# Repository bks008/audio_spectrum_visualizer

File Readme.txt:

Audio Spectrum Visualizer

Samples stereo analog audio and displays the frequency response on an 8x24 dot LED display.

Inputs:
USB-C PD

R/L RCA at audio line level

USB-C comes in at 20V. 
Supply rails:
3.3V digital supply
5V display supply
+/-6V analog supplies. +/-5V after LDO

R/L RCA has two identical channels
Gain stage
Unity gain stage to add offset (0-5V signal)
Anti Aliasing Low Pass Filter stage
Sampled using ADC121S101 over SPI

Digital Section is anything in the Arduino Nano pinout/form factor. Going with an STM32 NUCLEO-L432KC

Nucleo drives LEDs using I2C to three HT16K33A (borrowing architecture from Adafruit). 

Includes rotary encoder for brightness control and pushbutton.

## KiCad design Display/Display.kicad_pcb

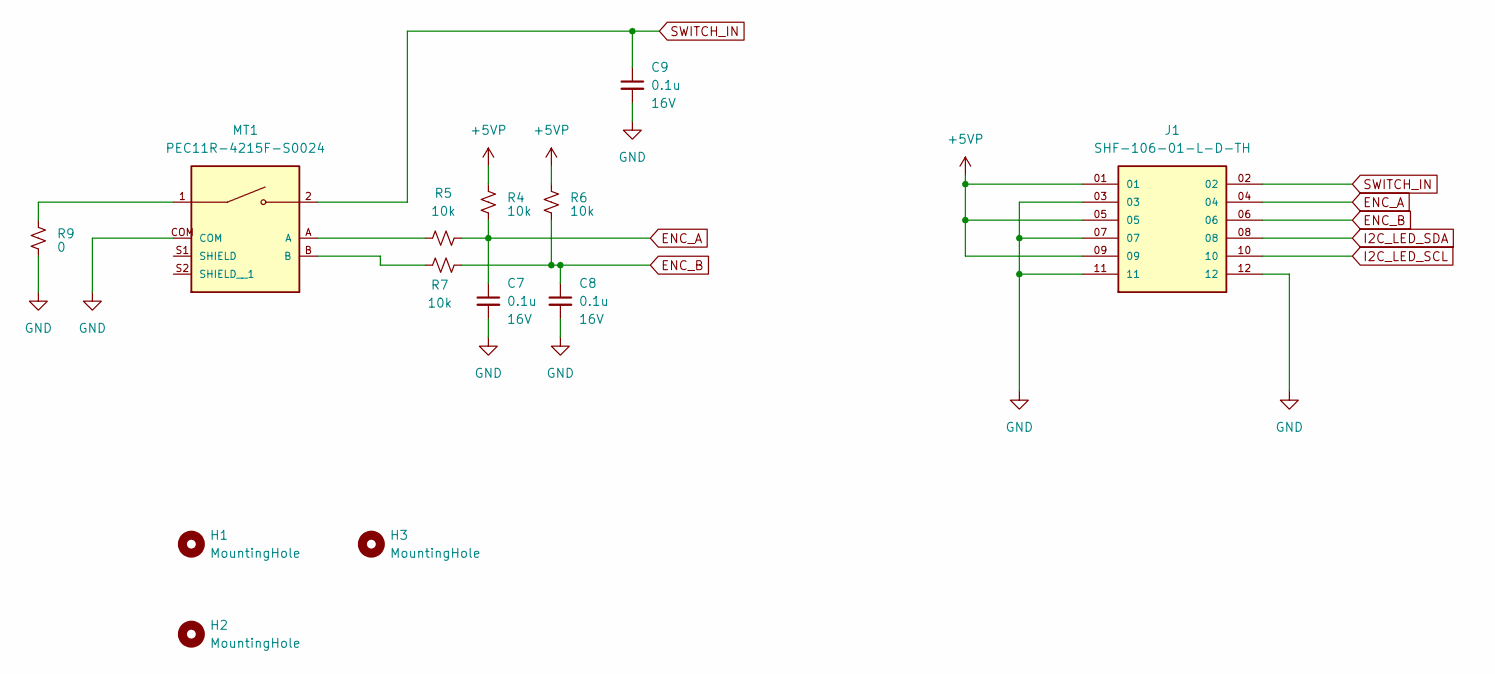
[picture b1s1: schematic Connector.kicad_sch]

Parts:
C7, C8, C9: 0.1u; C_0805_2012Metric_Pad1.18x1.45mm_HandSolder; Voltage 16V; Part Number 0805YC104MAT2A
H1, H2, H3: MountingHole; MountingHole_2.2mm_M2_Pad
J1: SHF-106-01-L-D-TH; SAMTEC_SHF-106-01-L-D-TH; PARTREV R
MT1: PEC11R-4215F-S0024; XDCR_PEC11R-4215F-S0024; PARTREV Rev. 09/19
R4, R5, R6, R7: 10k; R_0805_2012Metric_Pad1.20x1.40mm_HandSolder; Part Number CRCW080510K0FKEA
R9: 0; R_0805_2012Metric_Pad1.20x1.40mm_HandSolder; Part Number CRCW08050000FKEA

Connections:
+5VP: J1.01, J1.05, J1.09, R4.1, R6.1; also elsewhere on the board
ENC_A: C7.1, J1.04, R4.2, R5.2
ENC_B: C8.1, J1.06, R6.2, R7.2
GND: C7.2, C8.2, C9.2, J1.03, J1.07, J1.11, J1.12, MT1.COM, R9.2; also elsewhere on the board
I2C_LED_SCL: J1.10; also elsewhere on the board
I2C_LED_SDA: J1.08; also elsewhere on the board
unnamed: MT1.1, R9.1
unnamed: MT1.A, R5.1
unnamed: MT1.B, R7.1
SWITCH_IN: C9.1, J1.02, MT1.2

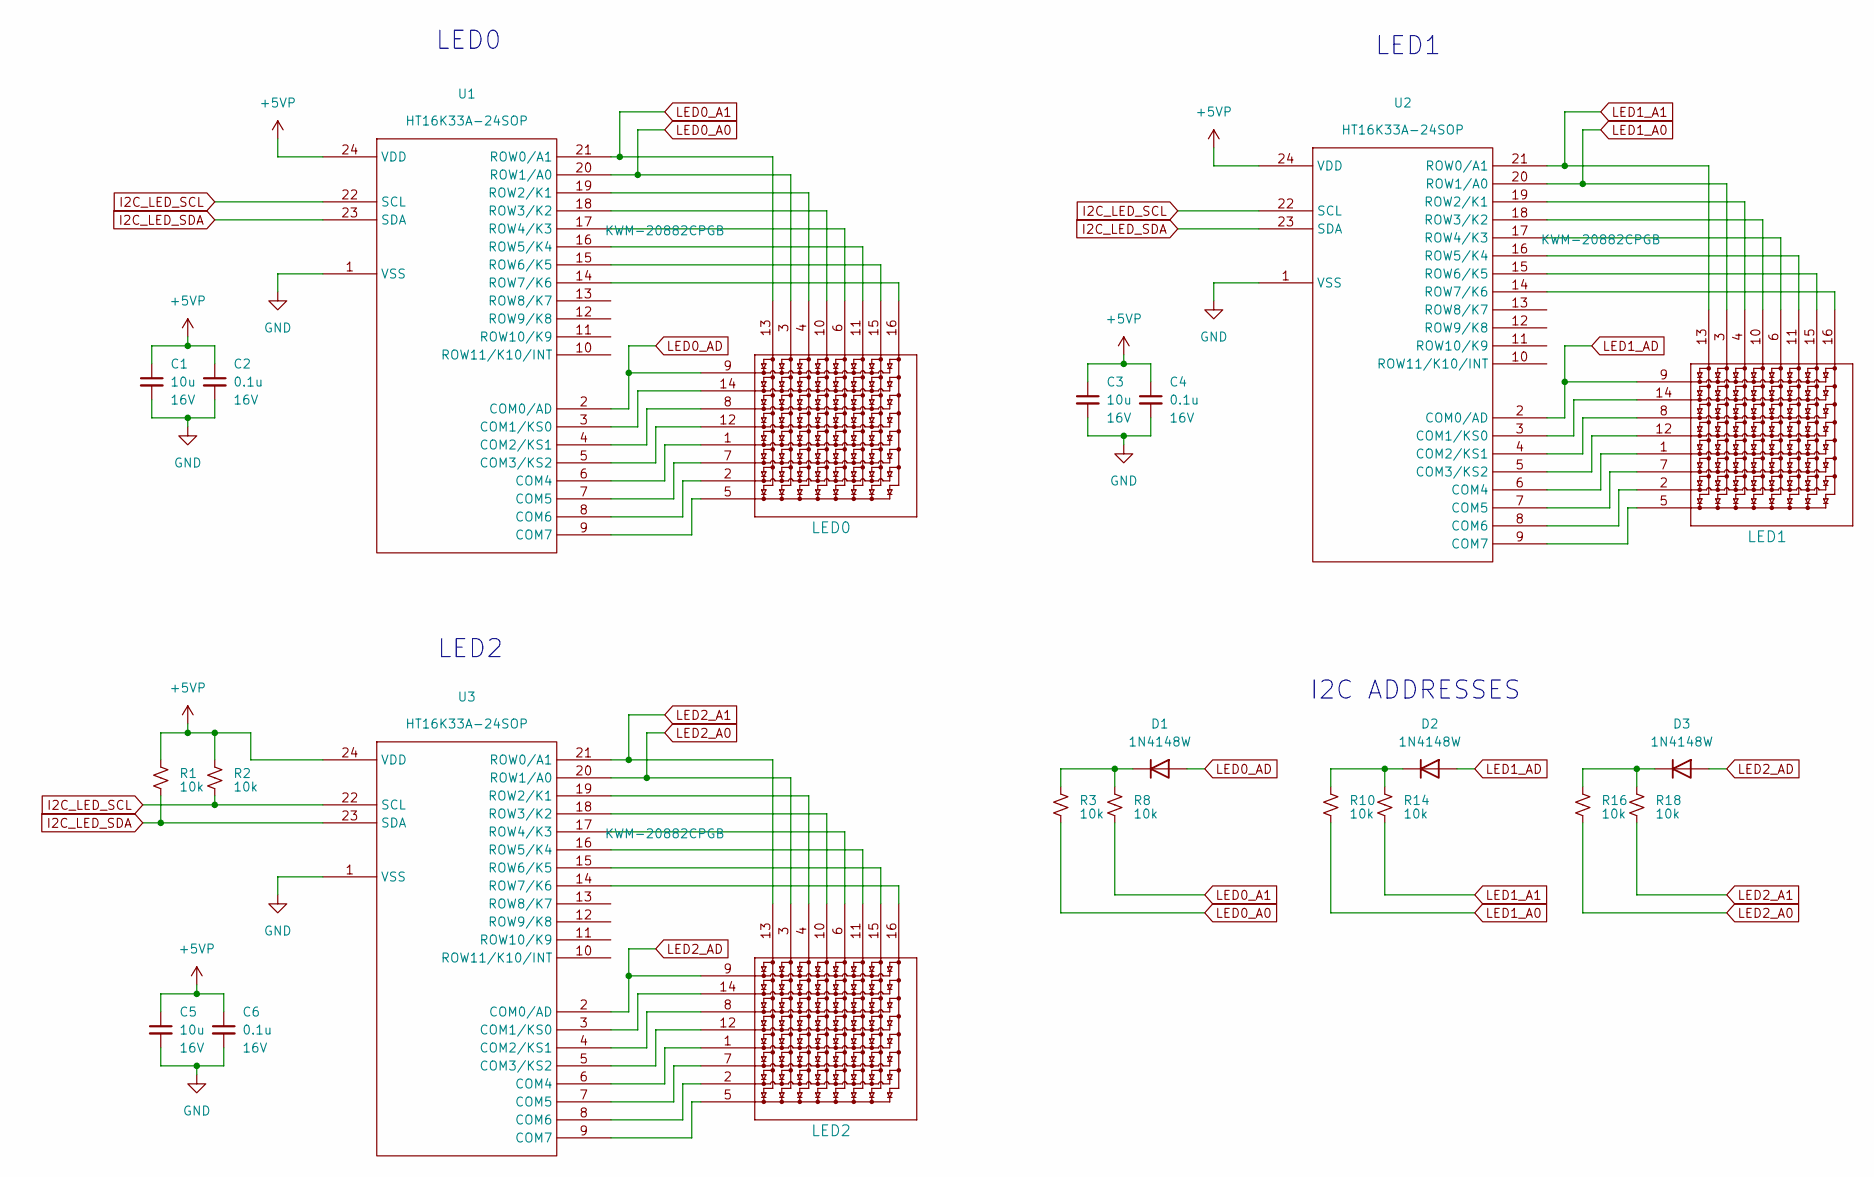
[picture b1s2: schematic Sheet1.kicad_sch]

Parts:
C1, C3, C5: 10u; C_0805_2012Metric_Pad1.18x1.45mm_HandSolder; Voltage 16V; Part Number 0805YC106MAT2A
C2, C4, C6: 0.1u; C_0805_2012Metric_Pad1.18x1.45mm_HandSolder; Voltage 16V; Part Number 0805YC104MAT2A
D1, D2: 1N4148W; D_SOD-523
D3: 1N4148W; D_SOD-523; Part Number 1N4148W
LED0, LED1, LED2: KWM-R30881CBB; KWM-20882AUGB; Part Number KWM-20882CPGB
R1, R2, R3, R8, R10, R14, R16, R18: 10k; R_0805_2012Metric_Pad1.20x1.40mm_HandSolder; Part Number CRCW080510K0FKEA
U1, U2, U3: SOP-24_7.5x15.4mm_P1.27mm; Part Number HT16K33A-24SOP

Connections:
+5VP: C1.1, C2.1, C3.1, C4.1, C5.1, C6.1, R1.1, R2.1, U1.24 (VDD), U2.24 (VDD), U3.24 (VDD); also elsewhere on the board
GND: C1.2, C2.2, C3.2, C4.2, C5.2, C6.2, U1.1 (VSS), U2.1 (VSS), U3.1 (VSS); also elsewhere on the board
I2C_LED_SCL: R2.2, U1.22 (SCL), U2.22 (SCL), U3.22 (SCL); also elsewhere on the board
I2C_LED_SDA: R1.2, U1.23 (SDA), U2.23 (SDA), U3.23 (SDA); also elsewhere on the board
LED0_A0: LED0.3 (ANODE_2), R3.2, U1.20 (ROW1/A0)
LED0_A1: LED0.13 (ANODE_1), R8.2, U1.21 (ROW0/A1)
LED0_AD: D1.2 (A), LED0.9 (CATHODE_1), U1.2 (COM0/AD)
LED1_A0: LED1.3 (ANODE_2), R10.2, U2.20 (ROW1/A0)
LED1_A1: LED1.13 (ANODE_1), R14.2, U2.21 (ROW0/A1)
LED1_AD: D2.2 (A), LED1.9 (CATHODE_1), U2.2 (COM0/AD)
LED2_A0: LED2.3 (ANODE_2), R16.2, U3.20 (ROW1/A0)
LED2_A1: LED2.13 (ANODE_1), R18.2, U3.21 (ROW0/A1)
LED2_AD: D3.2 (A), LED2.9 (CATHODE_1), U3.2 (COM0/AD)
unnamed: D1.1 (K), R3.1, R8.1
unnamed: D2.1 (K), R10.1, R14.1
unnamed: D3.1 (K), R16.1, R18.1
unnamed: LED0.4 (ANODE_3), U1.19 (ROW2/K1)
unnamed: LED0.10 (ANODE_4), U1.18 (ROW3/K2)
unnamed: LED0.6 (ANODE_5), U1.17 (ROW4/K3)
unnamed: LED0.11 (ANODE_6), U1.16 (ROW5/K4)
unnamed: LED0.15 (ANODE_7), U1.15 (ROW6/K5)
unnamed: LED0.16 (ANODE_8), U1.14 (ROW7/K6)
unnamed: LED0.14 (CATHODE_2), U1.3 (COM1/KS0)
unnamed: LED0.8 (CATHODE_3), U1.4 (COM2/KS1)
unnamed: LED0.12 (CATHODE_4), U1.5 (COM3/KS2)
unnamed: LED0.1 (CATHODE_5), U1.6 (COM4)
unnamed: LED0.7 (CATHODE_6), U1.7 (COM5)
unnamed: LED0.2 (CATHODE_7), U1.8 (COM6)
unnamed: LED0.5 (CATHODE_8), U1.9 (COM7)
unnamed: LED1.4 (ANODE_3), U2.19 (ROW2/K1)
unnamed: LED1.10 (ANODE_4), U2.18 (ROW3/K2)
unnamed: LED1.6 (ANODE_5), U2.17 (ROW4/K3)
unnamed: LED1.11 (ANODE_6), U2.16 (ROW5/K4)
unnamed: LED1.15 (ANODE_7), U2.15 (ROW6/K5)
unnamed: LED1.16 (ANODE_8), U2.14 (ROW7/K6)
unnamed: LED1.14 (CATHODE_2), U2.3 (COM1/KS0)
unnamed: LED1.8 (CATHODE_3), U2.4 (COM2/KS1)
unnamed: LED1.12 (CATHODE_4), U2.5 (COM3/KS2)
unnamed: LED1.1 (CATHODE_5), U2.6 (COM4)
unnamed: LED1.7 (CATHODE_6), U2.7 (COM5)
unnamed: LED1.2 (CATHODE_7), U2.8 (COM6)
unnamed: LED1.5 (CATHODE_8), U2.9 (COM7)
unnamed: LED2.4 (ANODE_3), U3.19 (ROW2/K1)
unnamed: LED2.10 (ANODE_4), U3.18 (ROW3/K2)
unnamed: LED2.6 (ANODE_5), U3.17 (ROW4/K3)
unnamed: LED2.11 (ANODE_6), U3.16 (ROW5/K4)
unnamed: LED2.15 (ANODE_7), U3.15 (ROW6/K5)
unnamed: LED2.16 (ANODE_8), U3.14 (ROW7/K6)
unnamed: LED2.14 (CATHODE_2), U3.3 (COM1/KS0)
unnamed: LED2.8 (CATHODE_3), U3.4 (COM2/KS1)
unnamed: LED2.12 (CATHODE_4), U3.5 (COM3/KS2)
unnamed: LED2.1 (CATHODE_5), U3.6 (COM4)
unnamed: LED2.7 (CATHODE_6), U3.7 (COM5)
unnamed: LED2.2 (CATHODE_7), U3.8 (COM6)
unnamed: LED2.5 (CATHODE_8), U3.9 (COM7)

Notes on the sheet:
LED1
I2C ADDRESSES
LED0
LED2

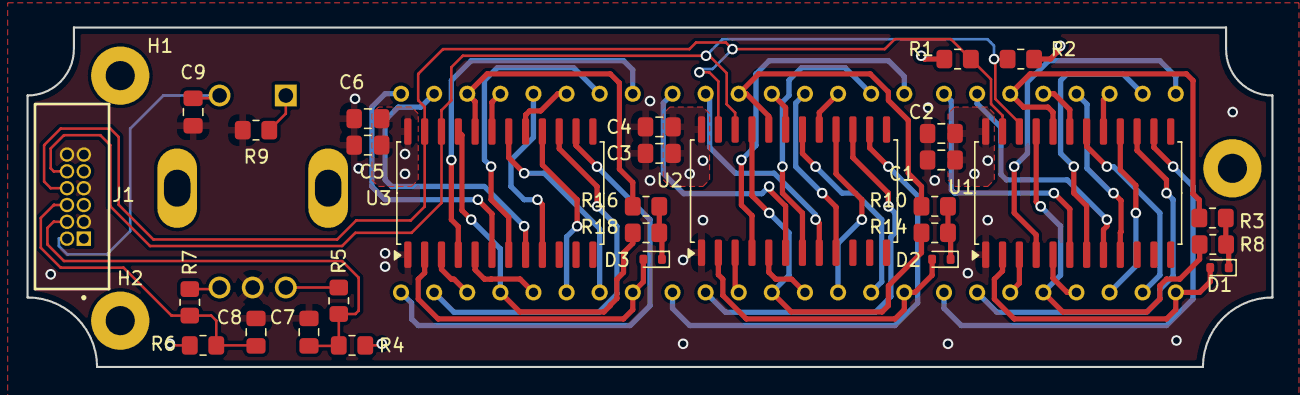
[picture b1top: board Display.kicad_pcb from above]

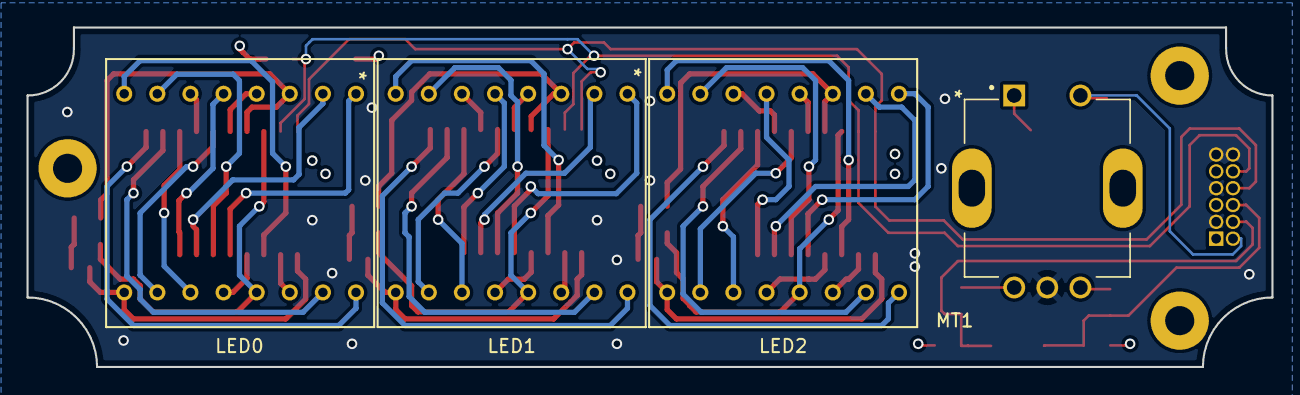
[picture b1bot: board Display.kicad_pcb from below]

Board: 4 copper layers, 94.0 x 25.6 mm, 36 parts (4 on the bottom side), 61 nets.

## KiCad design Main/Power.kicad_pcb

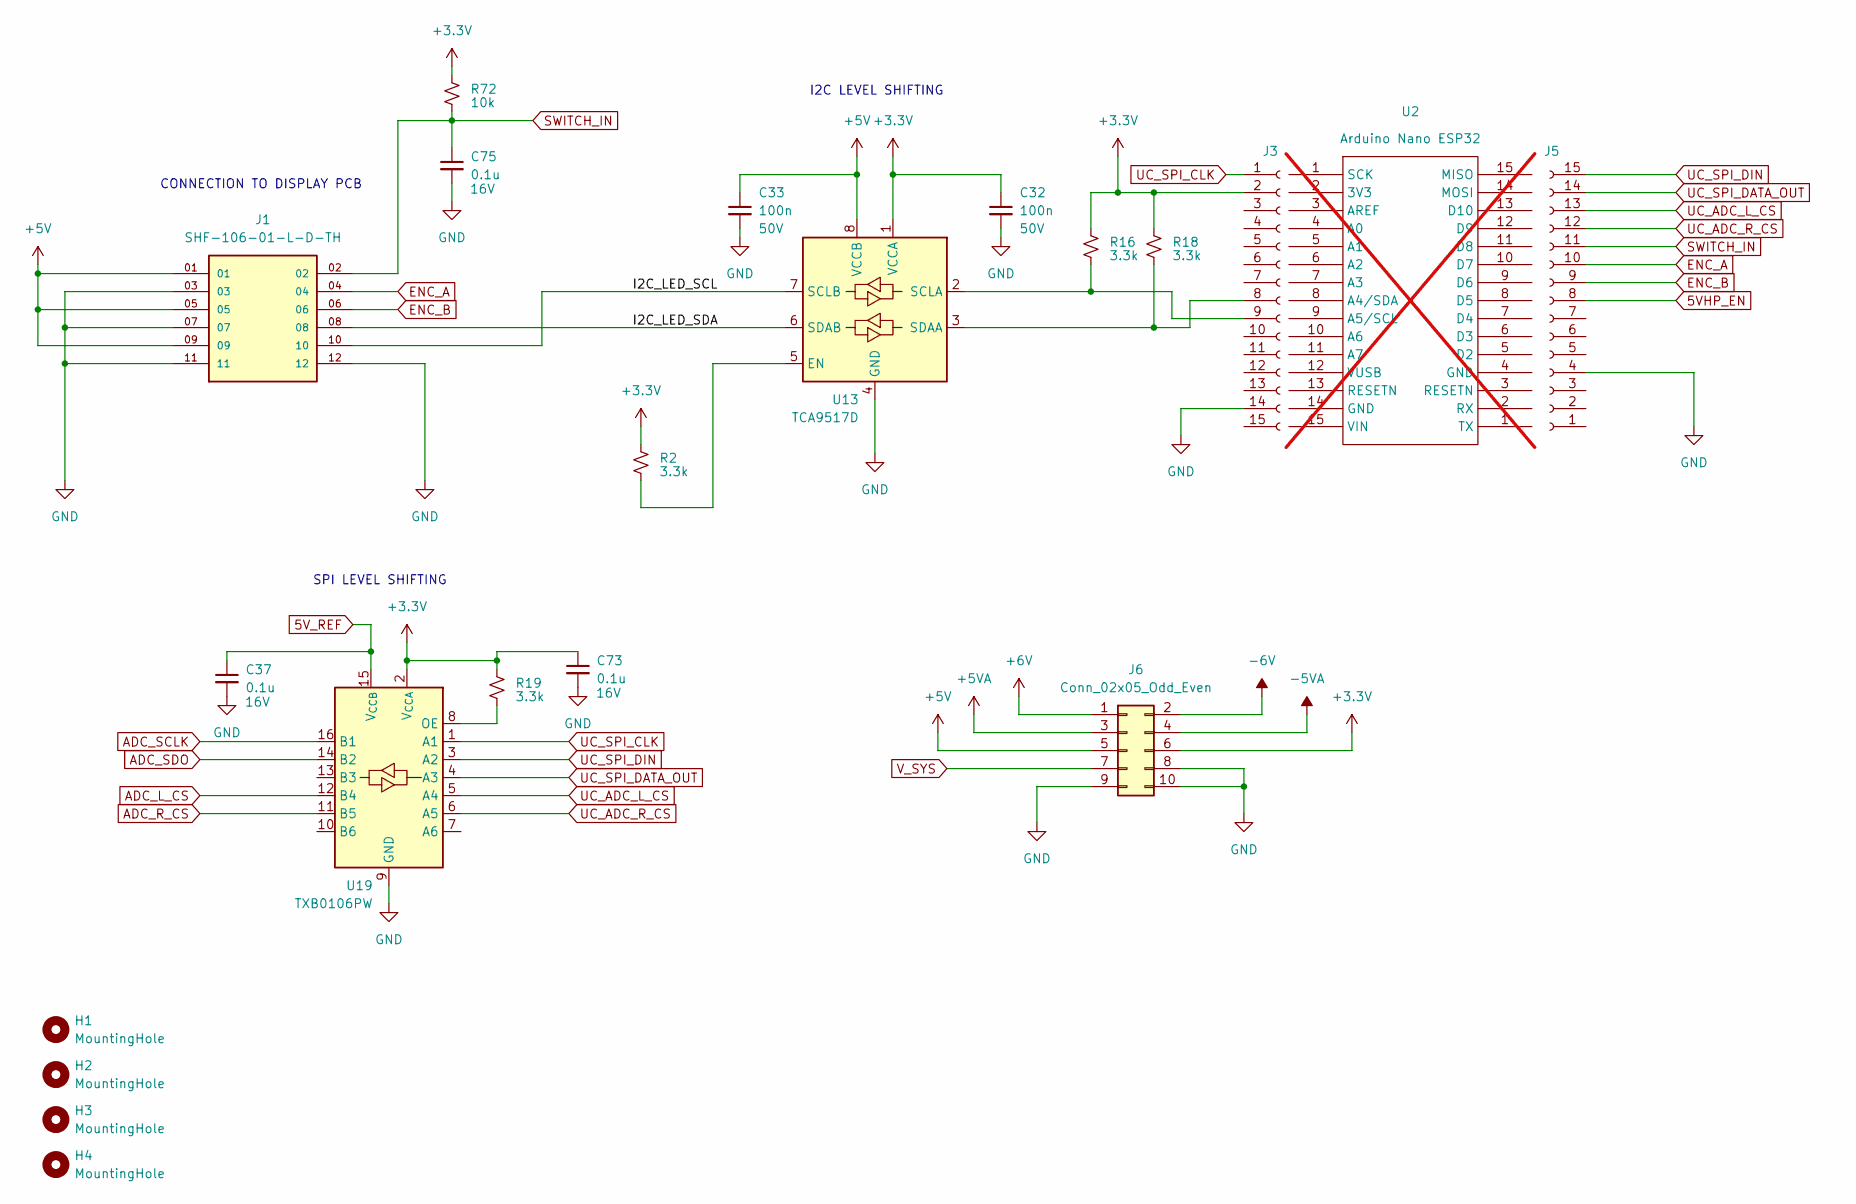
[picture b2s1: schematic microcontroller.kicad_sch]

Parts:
C32, C33: 100n; C_0805_2012Metric_Pad1.18x1.45mm_HandSolder; Voltage 50V; Part Number GRM21BR71H104KA01L
C37, C73, C75: 0.1u; C_0805_2012Metric_Pad1.18x1.45mm_HandSolder; Voltage 16V; Part Number 0805YC104MAT2A
H1, H2, H3, H4: MountingHole; MountingHole_2.5mm
J1: SHF-106-01-L-D-TH; SAMTEC_SHF-106-01-L-D-TH; PARTREV R
J3, J5: Conn_01x15_Socket; PinSocket_1x15_P2.54mm_Vertical
J6: Conn_02x05_Odd_Even; PinHeader_2x05_P1.27mm_Vertical
R2, R16, R18, R19: 3.3k; R_0805_2012Metric_HandSolder; Part Number CRCW08053K30FKEA
R72: 10k; R_0805_2012Metric_HandSolder
U2: Arduino_Nano_WithMountingHoles; Part Number Arduino Nano ESP32; not fitted
U13: TCA9517D; SOIC-8_3.9x4.9mm_P1.27mm; Part Number TCA9517D
U19: TXB0106PW; TSSOP-16_4.4x5mm_P0.65mm; Part Number TXB0106PW

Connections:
5VHP_EN: J5.8; also elsewhere on the board
5V_REF: C37.1, U19.15 (V_{CCB}); also elsewhere on the board
+3.3V: C32.1, C73.1, J3.2, J6.6, R2.2, R16.2, R18.2, R19.2, R72.2, U13.1 (VCCA), U19.2 (V_{CCA}); also elsewhere on the board
+5V: C33.1, J1.01, J1.05, J1.09, J6.5, U13.8 (VCCB); also elsewhere on the board
+5VA: J6.3; also elsewhere on the board
+6V: J6.1; also elsewhere on the board
-5VA: J6.4; also elsewhere on the board
-6V: J6.2; also elsewhere on the board
/Microcontroller/I2C_LED_SCL: J1.10, U13.7 (SCLB)
/Microcontroller/I2C_LED_SDA: J1.08, U13.6 (SDAB)
ADC_L_CS: U19.12 (B4); also elsewhere on the board
ADC_R_CS: U19.11 (B5); also elsewhere on the board
ADC_SCLK: U19.16 (B1); also elsewhere on the board
ADC_SDO: U19.14 (B2); also elsewhere on the board
ENC_A: J1.04, J5.10
ENC_B: J1.06, J5.9
GND: C32.2, C33.2, C37.2, C73.2, C75.2, J1.03, J1.07, J1.11, J1.12, J3.14, J5.4, J6.8, J6.9, J6.10, U13.4 (GND), U19.9 (GND); also elsewhere on the board
unnamed: J3.8, R18.1, U13.3 (SDAA)
unnamed: J3.9, R16.1, U13.2 (SCLA)
unnamed: R2.1, U13.5 (EN)
unnamed: R19.1, U19.8 (OE)
SWITCH_IN: C75.1, J1.02, J5.11, R72.1
UC_ADC_L_CS: J5.13, U19.5 (A4)
UC_ADC_R_CS: J5.12, U19.6 (A5)
UC_SPI_CLK: J3.1, U19.1 (A1)
UC_SPI_DATA_OUT: J5.14, U19.4 (A3)
UC_SPI_DIN: J5.15, U19.3 (A2)
V_SYS: J6.7; also elsewhere on the board

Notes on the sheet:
SPI LEVEL SHIFTING
CONNECTION TO DISPLAY PCB
I2C LEVEL SHIFTING

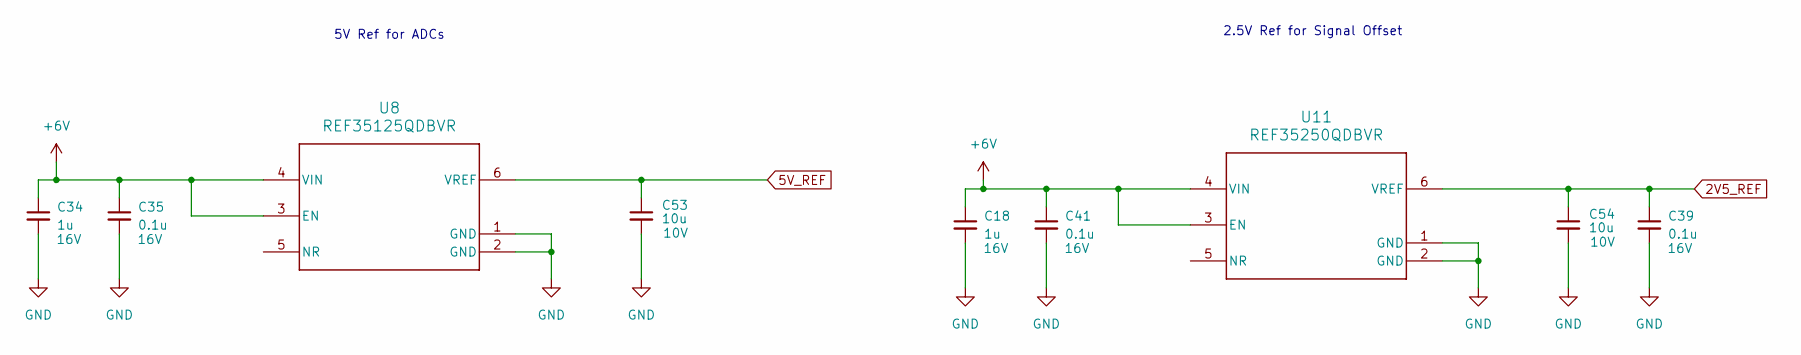
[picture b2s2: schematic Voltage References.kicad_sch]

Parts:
C18, C34: 1u; C_0805_2012Metric_Pad1.18x1.45mm_HandSolder; Voltage 16V; Part Number 0805YC105KAT2A
C35, C39, C41: 0.1u; C_0805_2012Metric_Pad1.18x1.45mm_HandSolder; Voltage 16V; Part Number 0805YC104MAT2A
C53, C54: 10u; C_0805_2012Metric_Pad1.18x1.45mm_HandSolder; Voltage 10V; Part Number MBASL21GBB7106KTNA18
U8: REF35125QDBVR; DBV0006A-IPC_A; Part Number REF35125QDBVR
U11: REF35250QDBVR; DBV0006A-IPC_A; Part Number REF35250QDBVR

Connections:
2V5_REF: C39.1, C54.1, U11.6 (VREF); also elsewhere on the board
5V_REF: C53.1, U8.6 (VREF); also elsewhere on the board
+6V: C18.1, C34.1, C35.1, C41.1, U8.3 (EN), U8.4 (VIN), U11.3 (EN), U11.4 (VIN); also elsewhere on the board
GND: C18.2, C34.2, C35.2, C39.2, C41.2, C53.2, C54.2, U8.1 (GND), U8.2 (GND), U11.1 (GND), U11.2 (GND); also elsewhere on the board

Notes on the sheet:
2.5V Ref for Signal Offset
5V Ref for ADCs

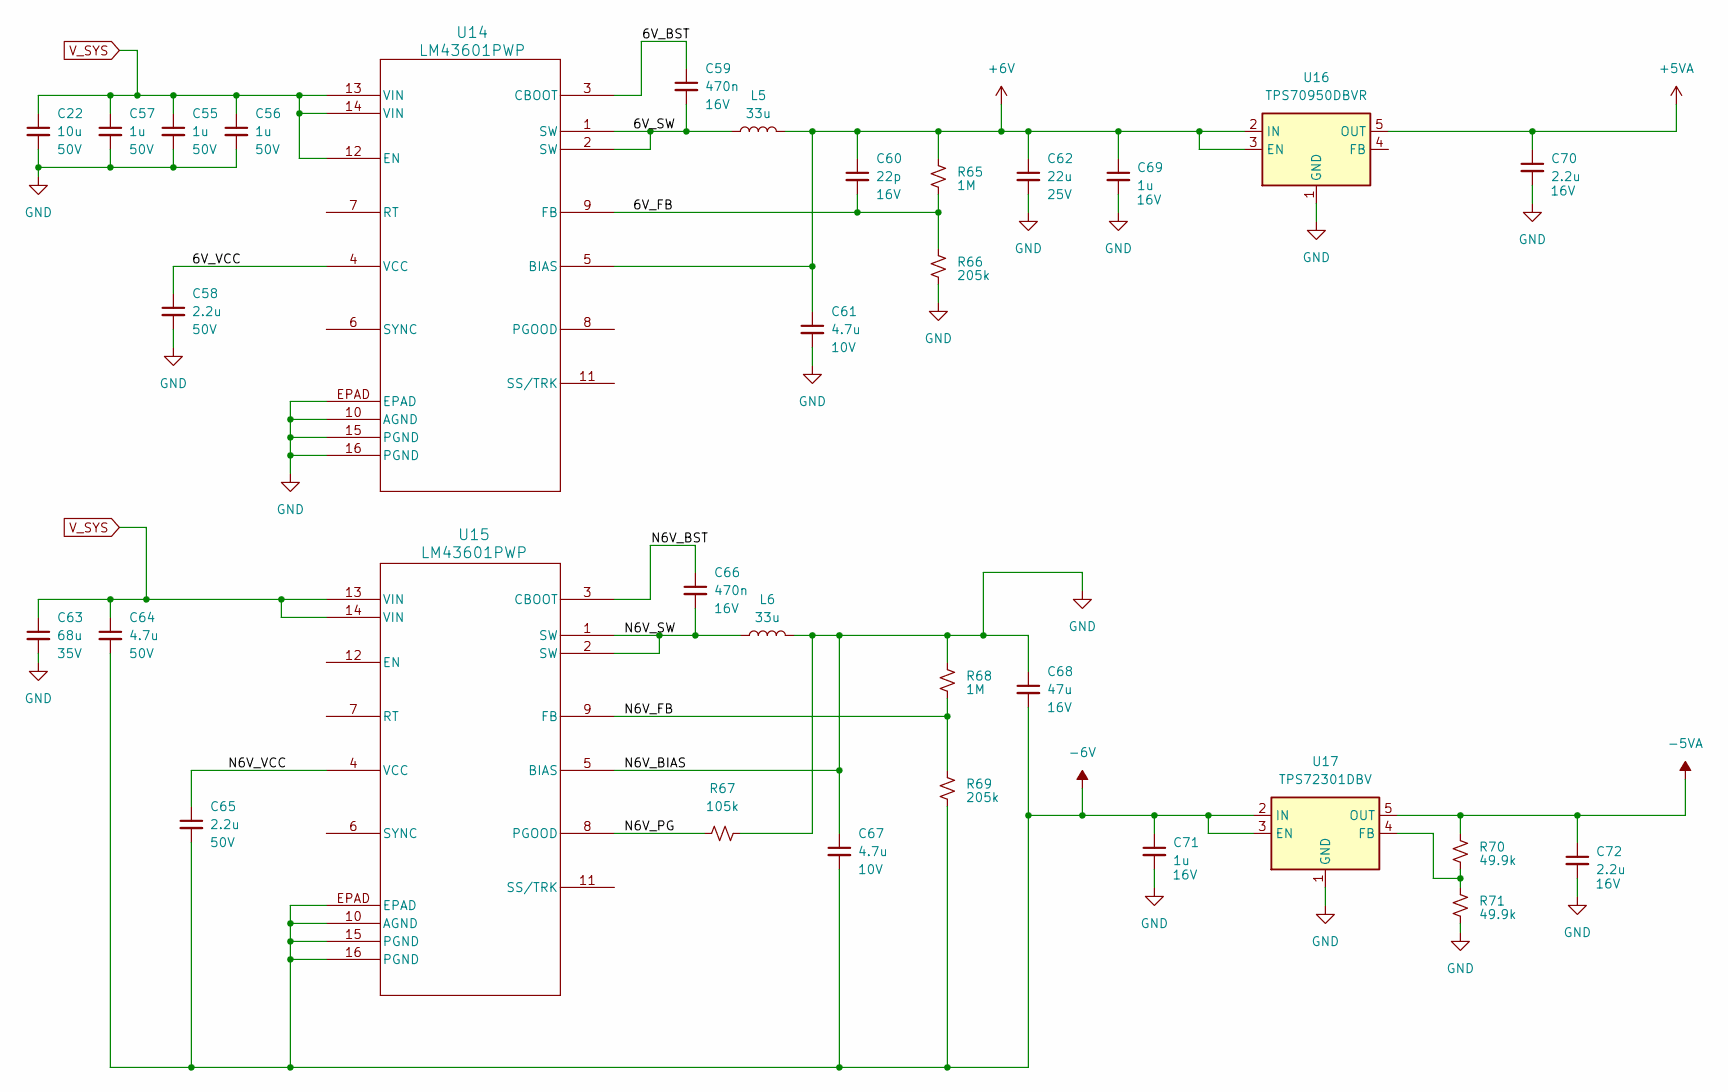
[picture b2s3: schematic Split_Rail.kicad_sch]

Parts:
C22: 10u; C_1206_3216Metric_Pad1.33x1.80mm_HandSolder; Voltage 50V; Part Number C3216X5R1H106K160AB
C55, C56, C57: 1u; C_0805_2012Metric_Pad1.18x1.45mm_HandSolder; Voltage 50V; Part Number 08055C105K4Z4A
C58, C65: 2.2u; C_0805_2012Metric_Pad1.18x1.45mm_HandSolder; Voltage 50V; Part Number 08055C225MAT2A
C59, C66: 470n; C_0805_2012Metric_Pad1.18x1.45mm_HandSolder; Voltage 16V; Part Number 0805YC474MAT2A
C60: 22p; C_0805_2012Metric_Pad1.18x1.45mm_HandSolder; Voltage 16V; Part Number 0805YA220JAT2A
C61, C67: 4.7u; C_0805_2012Metric_Pad1.18x1.45mm_HandSolder; Voltage 10V; Part Number LMK212B7475KG-T
C62: 22u; C_1206_3216Metric_Pad1.33x1.80mm_HandSolder; Voltage 25V; Part Number 12063D226KAT2A
C63: 68u; CP_Elec_6.3x7.7; Voltage 35V; Part Number UUD1V680MCL1GS
C64: 4.7u; C_0805_2012Metric_Pad1.18x1.45mm_HandSolder; Voltage 50V; Part Number C2012X5R1H475K125AB
C68: 47u; C_1210_3225Metric_Pad1.33x2.70mm_HandSolder; Voltage 16V; Part Number GRM32ER61C476KE15L
C69, C71: 1u; C_0805_2012Metric_Pad1.18x1.45mm_HandSolder; Voltage 16V; Part Number 0805YC105KAT2A
C70, C72: 2.2u; C_0805_2012Metric_Pad1.18x1.45mm_HandSolder; Voltage 16V; Part Number 0805YC225MAT2A
L5, L6: 33u; IND_BOURNS_SRN3015; Part Number SRN3015-330M
R65, R68: 1M; R_0805_2012Metric_Pad1.20x1.40mm_HandSolder
R66, R69: 205k; R_0805_2012Metric_Pad1.20x1.40mm_HandSolder
R67: 105k; R_0805_2012Metric_Pad1.20x1.40mm_HandSolder
R70, R71: 49.9k; R_0805_2012Metric_HandSolder
U14, U15: LM43601PWP; PWP16_TEX; Part Number LM43601PWP
U16: TPS70950DBVR; SOT-23-5; Part Number TPS70950DBVR
U17: TPS72301DBV; SOT-23-5; Part Number TPS72301DBV

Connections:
+5VA: C70.1, U16.5 (OUT); also elsewhere on the board
+6V: C60.1, C61.1, C62.1, C69.1, L5.2, R65.1, U14.5 (BIAS), U16.2 (IN), U16.3 (EN); also elsewhere on the board
-5VA: C72.1, R70.1, U17.5 (OUT); also elsewhere on the board
-6V: C64.2, C65.2, C67.2, C68.2, C71.1, R69.2, U15.10 (AGND), U15.15 (PGND), U15.16 (PGND), U15.EPAD, U17.2 (IN), U17.3 (EN); also elsewhere on the board
/Split Rail/6V_BST: C59.1, U14.3 (CBOOT)
/Split Rail/6V_FB: C60.2, R65.2, R66.1, U14.9 (FB)
/Split Rail/6V_SW: C59.2, L5.1, U14.1 (SW), U14.2 (SW)
/Split Rail/6V_VCC: C58.1, U14.4 (VCC)
/Split Rail/N6V_BST: C66.1, U15.3 (CBOOT)
/Split Rail/N6V_FB: R68.2, R69.1, U15.9 (FB)
/Split Rail/N6V_PG: R67.1, U15.8 (PGOOD)
/Split Rail/N6V_SW: C66.2, L6.1, U15.1 (SW), U15.2 (SW)
/Split Rail/N6V_VCC: C65.1, U15.4 (VCC)
GND: C22.2, C55.2, C56.2, C57.2, C58.2, C61.2, C62.2, C63.2, C67.1, C68.1, C69.2, C70.2, C71.2, C72.2, L6.2, R66.2, R67.2, R68.1, R71.2, U14.10 (AGND), U14.15 (PGND), U14.16 (PGND), U14.EPAD, U15.5 (BIAS), U16.1 (GND), U17.1 (GND); also elsewhere on the board
unnamed: R70.2, R71.1, U17.4 (FB)
V_SYS: C22.1, C55.1, C56.1, C57.1, C63.1, C64.1, U14.12 (EN), U14.13 (VIN), U14.14 (VIN), U15.13 (VIN), U15.14 (VIN); also elsewhere on the board

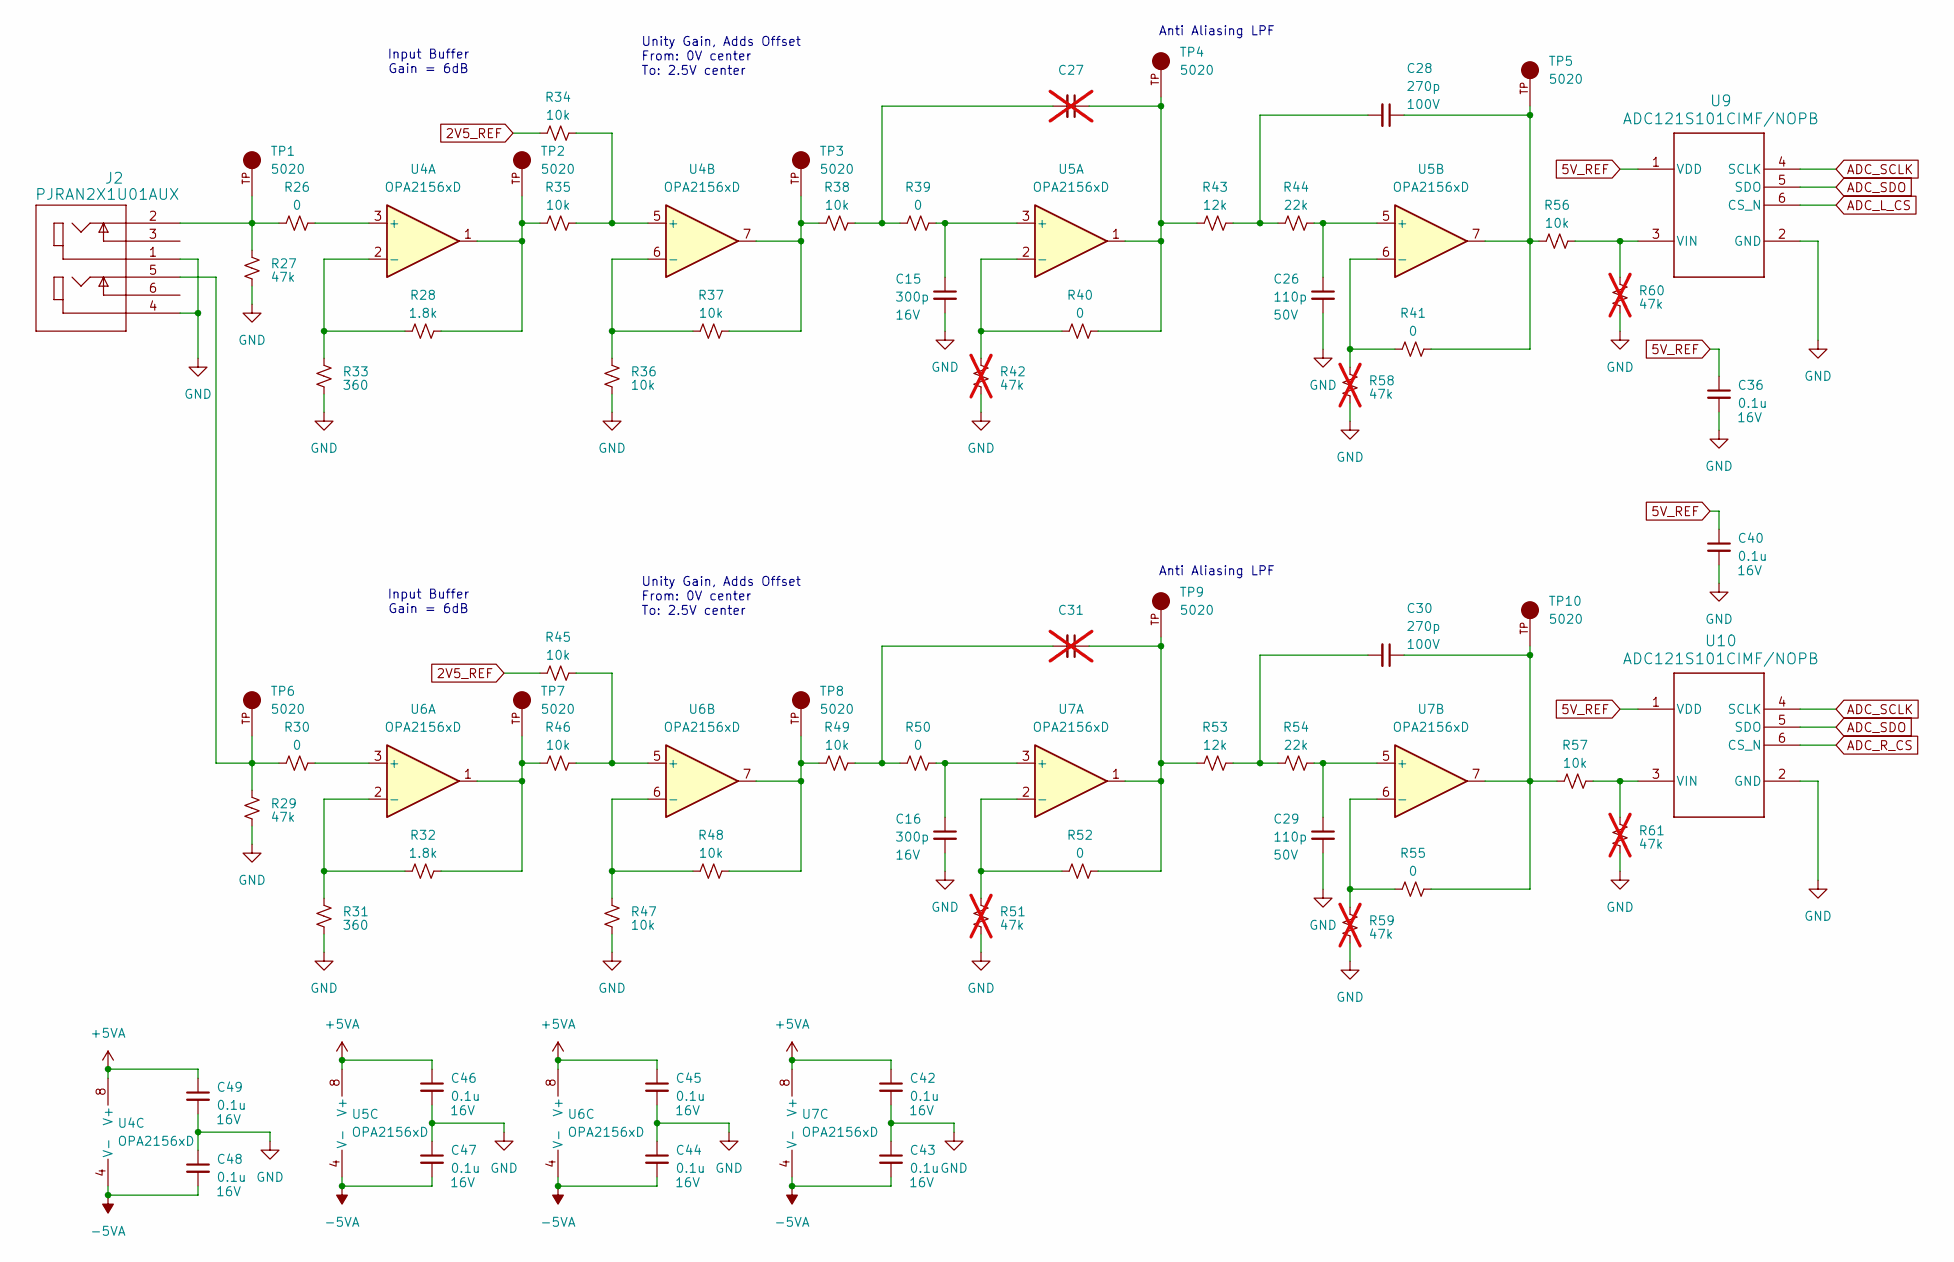
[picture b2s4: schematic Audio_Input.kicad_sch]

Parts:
C15, C16: 300p; C_0805_2012Metric_Pad1.18x1.45mm_HandSolder; Voltage 16V; Part Number 0805YC301JAT2A
C26, C29: 110p; C_0805_2012Metric_Pad1.18x1.45mm_HandSolder; Voltage 50V; Part Number 08055U111FAT2A
C27, C31: C_0805_2012Metric_Pad1.18x1.45mm_HandSolder; not fitted
C28, C30: 270p; C_0805_2012Metric_Pad1.18x1.45mm_HandSolder; Voltage 100V; Part Number 08051A271KAT2A
C36, C40, C42, C43, C44, C45, C46, C47, C48, C49: 0.1u; C_0805_2012Metric_Pad1.18x1.45mm_HandSolder; Voltage 16V; Part Number 0805YC104MAT2A
J2: PJRAN2X1U01AUX; CONN6_984x394_SWC_BS; Part Number PJRAN2X1U01AUX
R26, R30, R39, R40, R41, R50, R52, R55: 0; R_0805_2012Metric_HandSolder; Part Number CRCW08050000FKEA
R27, R29: 47k; R_0805_2012Metric_HandSolder; Part Number CRCW080547K0FKEA
R28, R32: 1.8k; R_0805_2012Metric_HandSolder; Part Number CRCW08051K80FKEA
R31, R33: 360; R_0805_2012Metric_HandSolder; Part Number CRCW0805360RFKEA
R34, R35, R36, R37, R38, R45, R46, R47, R48, R49, R56, R57: 10k; R_0805_2012Metric_HandSolder
R42, R51, R58, R59, R60, R61: 47k; R_0805_2012Metric_HandSolder; Part Number CRCW080547K0FKEA; not fitted
R43, R53: 12k; R_0805_2012Metric_HandSolder; Part Number CRCW080512K0FKEA
R44, R54: 22k; R_0805_2012Metric_HandSolder; Part Number CRCW080522K0FKEA
TP1, TP2, TP3, TP4, TP5, TP6, TP7, TP8, TP9, TP10: 5020; KEYSTONE_5020; PARTREV C
U4, U5, U6, U7: OPA2156xD; SOIC-8_3.9x4.9mm_P1.27mm; Part Number OPA2156xD
U9, U10: ADC121S101CIMF/NOPB; DBV0006A_N; Part Number ADC121S101CIMF/NOPB

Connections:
2V5_REF: R34.1, R45.1; also elsewhere on the board
5V_REF: C36.1, C40.1, U9.1 (VDD), U10.1 (VDD); also elsewhere on the board
+5VA: C42.1, C45.1, C46.1, C49.1, U4.8 (V+), U5.8 (V+), U6.8 (V+), U7.8 (V+); also elsewhere on the board
-5VA: C43.2, C44.2, C47.2, C48.2, U4.4 (V-), U5.4 (V-), U6.4 (V-), U7.4 (V-); also elsewhere on the board
ADC_L_CS: U9.6 (CS_N); also elsewhere on the board
ADC_R_CS: U10.6 (CS_N); also elsewhere on the board
ADC_SCLK: U9.4 (SCLK), U10.4 (SCLK); also elsewhere on the board
ADC_SDO: U9.5 (SDO), U10.5 (SDO); also elsewhere on the board
GND: C15.2, C16.2, C26.2, C29.2, C36.2, C40.2, C42.2, C43.1, C44.1, C45.2, C46.2, C47.1, C48.1, C49.2, J2.1, J2.4, R27.1, R29.1, R31.1, R33.1, R36.1, R42.1, R47.1, R51.1, R58.1, R59.1, R60.1, R61.1, U9.2 (GND), U10.2 (GND); also elsewhere on the board
unnamed: C27.1, R40.2, R43.1, TP4.TP, U5.1
unnamed: C27.2, R38.2, R39.1
unnamed: C28.1, R41.2, R56.1, TP5.TP, U5.7
unnamed: C28.2, R43.2, R44.1
unnamed: C30.1, R55.2, R57.1, TP10.TP, U7.7
unnamed: C30.2, R53.2, R54.1
unnamed: C31.1, R52.2, R53.1, TP9.TP, U7.1
unnamed: C31.2, R49.2, R50.1
unnamed: J2.2, R26.1, R27.2, TP1.TP
unnamed: J2.5, R29.2, R30.1, TP6.TP
unnamed: R28.2, R35.1, TP2.TP, U4.1
unnamed: R32.2, R46.1, TP7.TP, U6.1
unnamed: R37.2, R38.1, TP3.TP, U4.7
unnamed: R48.2, R49.1, TP8.TP, U6.7
unnamed: R26.2, U4.3 (+)
unnamed: R28.1, R33.2, U4.2 (-)
unnamed: R34.2, R35.2, U4.5 (+)
unnamed: R36.2, R37.1, U4.6 (-)
unnamed: C15.1, R39.2, U5.3 (+)
unnamed: R40.1, R42.2, U5.2 (-)
unnamed: C26.1, R44.2, U5.5 (+)
unnamed: R41.1, R58.2, U5.6 (-)
unnamed: R30.2, U6.3 (+)
unnamed: R31.2, R32.1, U6.2 (-)
unnamed: R45.2, R46.2, U6.5 (+)
unnamed: R47.2, R48.1, U6.6 (-)
unnamed: C16.1, R50.2, U7.3 (+)
unnamed: R51.2, R52.1, U7.2 (-)
unnamed: C29.1, R54.2, U7.5 (+)
unnamed: R55.1, R59.2, U7.6 (-)
unnamed: R56.2, R60.2, U9.3 (VIN)
unnamed: R57.2, R61.2, U10.3 (VIN)

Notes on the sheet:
Unity Gain, Adds Offset From: 0V center To: 2.5V center
Anti Aliasing LPF
Input Buffer Gain = 6dB
